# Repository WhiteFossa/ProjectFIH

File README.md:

# ProjectFIH
Digitally-controlled thermostat for heating outdoor hardware

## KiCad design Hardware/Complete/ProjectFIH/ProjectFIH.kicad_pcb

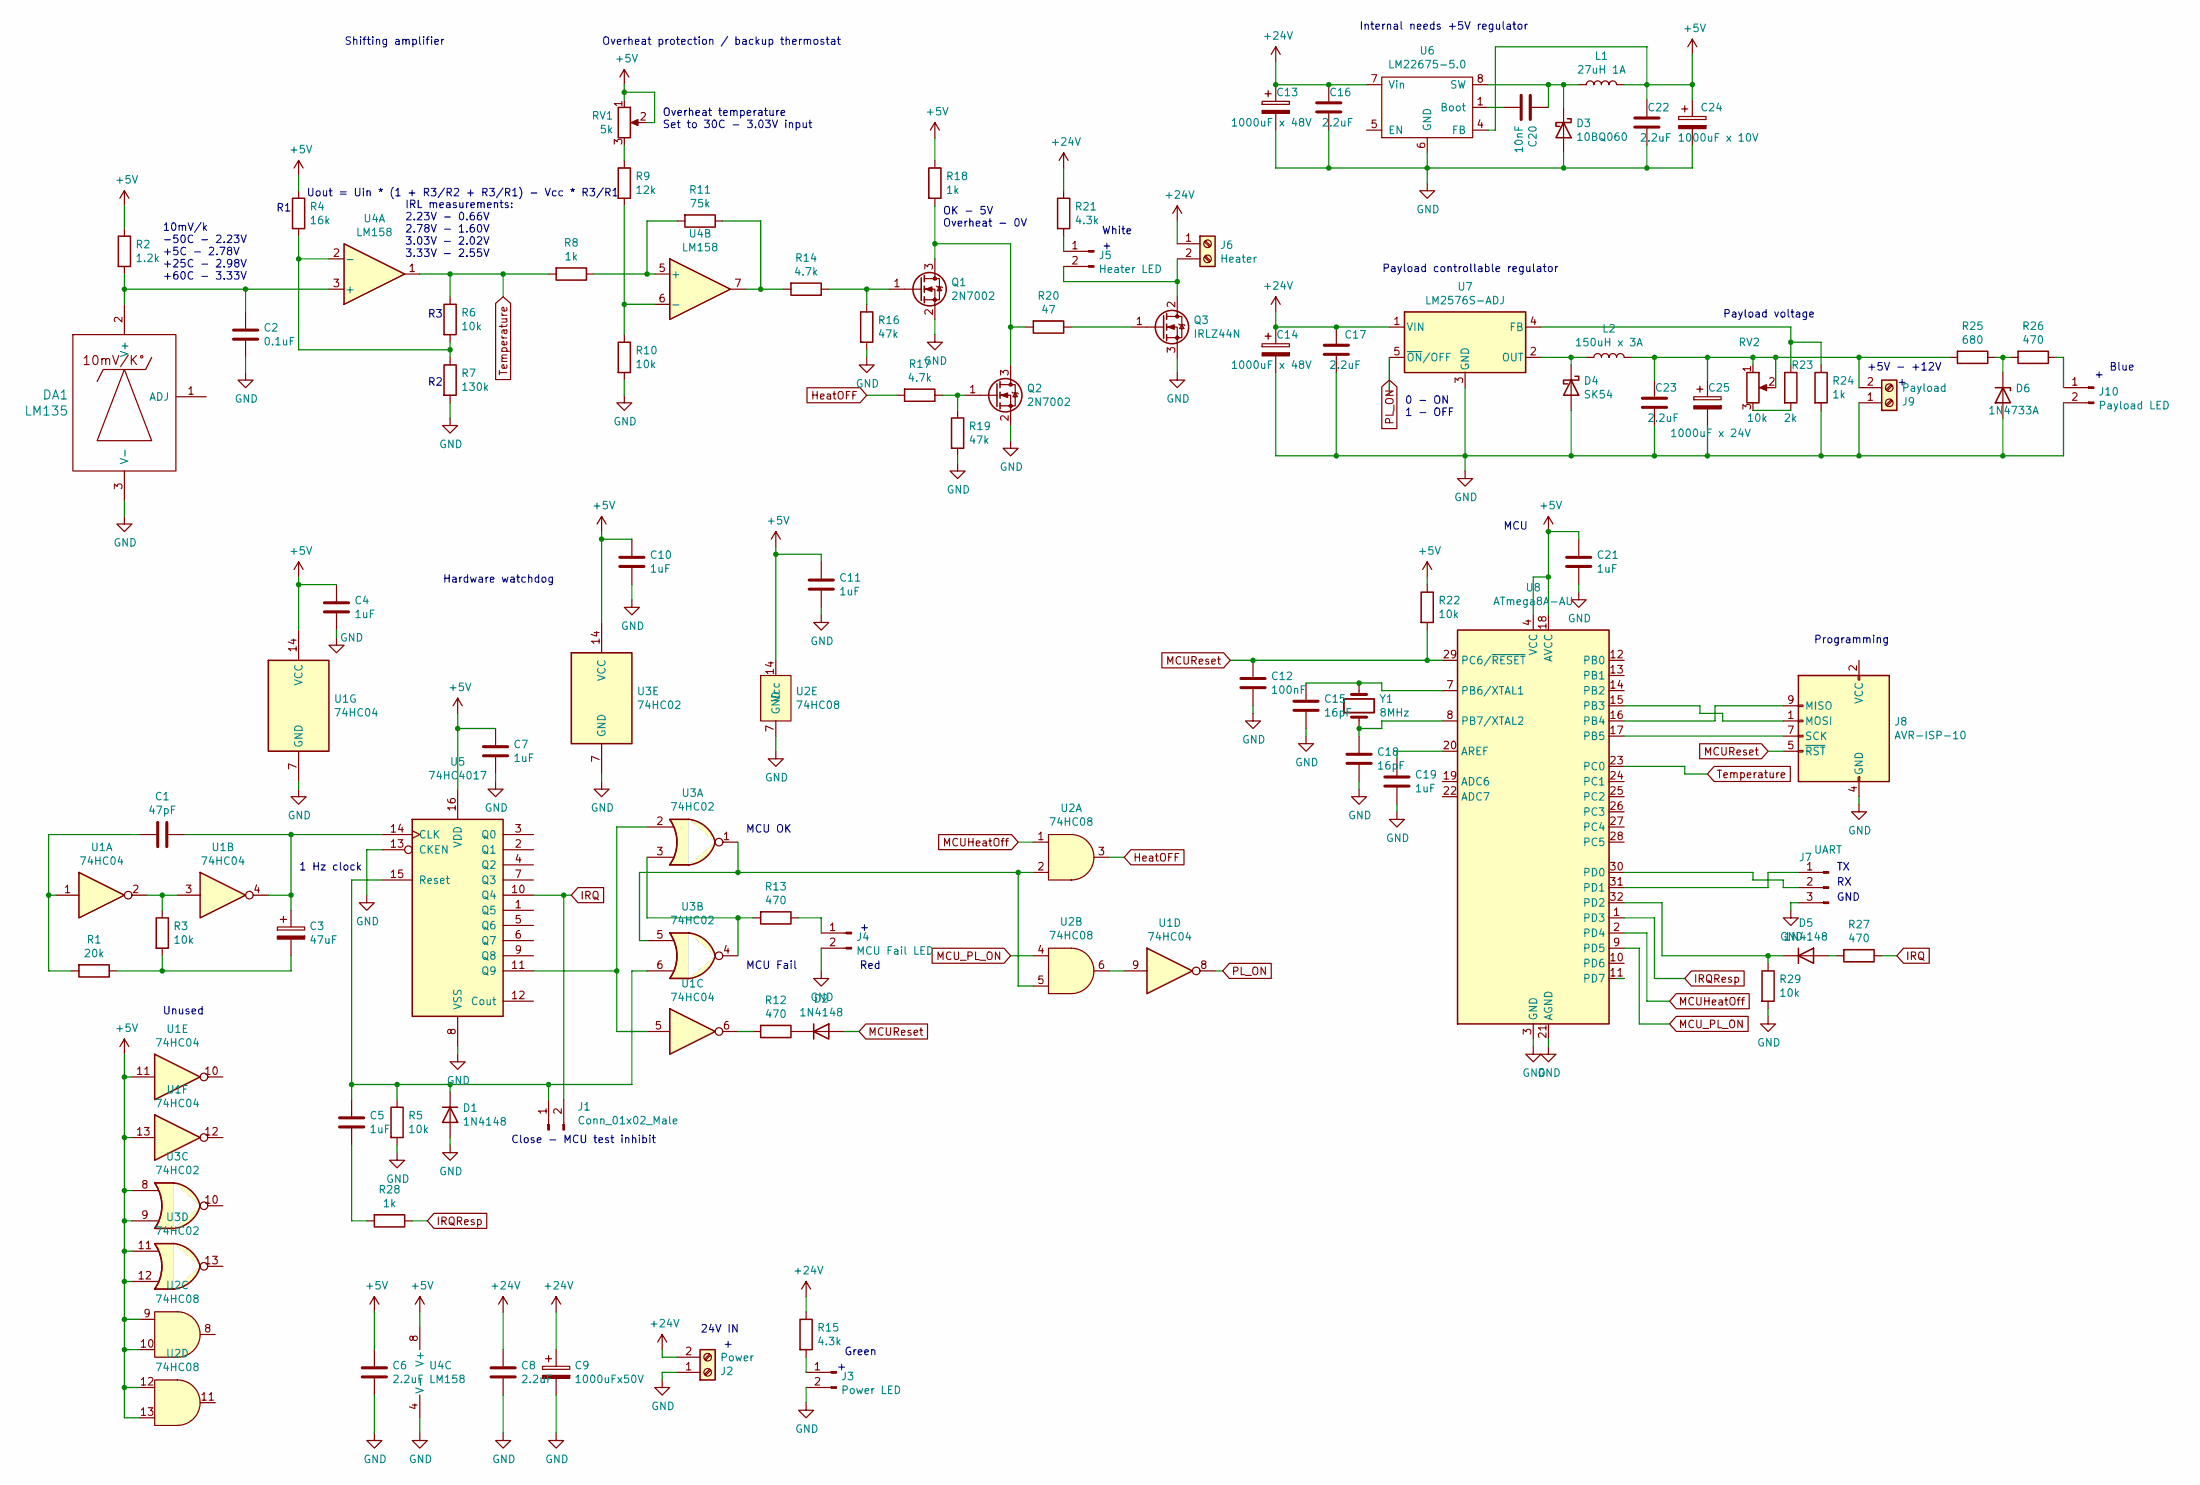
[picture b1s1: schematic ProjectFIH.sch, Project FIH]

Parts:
C1: 47pF; C_0805_2012Metric_Pad1.15x1.40mm_HandSolder
C2: 0.1uF; C_0805_2012Metric_Pad1.15x1.40mm_HandSolder
C3: 47uF; CP_Elec_4x5.7
C4, C5, C7, C10, C11, C19, C21: 1uF; C_0805_2012Metric_Pad1.15x1.40mm_HandSolder
C6, C8, C16, C17, C22, C23: 2.2uF; C_0805_2012Metric_Pad1.15x1.40mm_HandSolder
C9: 1000uFx50V; CP_Radial_D12.5mm_P5.00mm
C12: 100nF; C_0805_2012Metric_Pad1.15x1.40mm_HandSolder
C13, C14: 1000uF x 48V; CP_Radial_D12.5mm_P5.00mm
C15, C18: 16pF; C_0805_2012Metric_Pad1.15x1.40mm_HandSolder
C20: 10nF; C_0805_2012Metric_Pad1.15x1.40mm_HandSolder
C24: 1000uF x 10V; CP_Radial_D10.0mm_P5.00mm
C25: 1000uF x 24V; CP_Radial_D10.0mm_P5.00mm
D1, D2, D5: 1N4148; D_1210_3225Metric
D3: 10BQ060; D_SMB
D4: SK54; D_SMC
D6: 1N4733A; D_1210_3225Metric
DA1: LM135; TO-92
J1: Conn_01x02_Male; PinHeader_1x02_P2.54mm_Vertical
J2: Power; TerminalBlock_Altech_AK300-2_P5.00mm
J3: Power LED; PinHeader_1x02_P2.54mm_Vertical
J4: MCU Fail LED; PinHeader_1x02_P2.54mm_Vertical
J5: Heater LED; PinHeader_1x02_P2.54mm_Vertical
J6: Heater; TerminalBlock_Altech_AK300-2_P5.00mm
J7: UART; PinHeader_1x03_P2.54mm_Vertical
J8: AVR-ISP-10; IDC-Header_2x05_P2.54mm_Vertical
J9: Payload; TerminalBlock_Altech_AK300-2_P5.00mm
J10: Payload LED; PinHeader_1x02_P2.54mm_Vertical
L1: 27uH 1A; L_Radial_D10.0mm_P5.00mm_Fastron_07M
L2: 150uH x 3A; L_Radial_D16.8mm_P11.43mm_Vishay_IHB-1
Q1, Q2: 2N7002; SOT-23
Q3: IRLZ44N; TO-220-3_Horizontal_TabDown
R1: 20k; R_0805_2012Metric_Pad1.15x1.40mm_HandSolder
R2: 1.2k; R_0805_2012Metric_Pad1.15x1.40mm_HandSolder
R3, R5, R6, R10, R22, R29: 10k; R_0805_2012Metric_Pad1.15x1.40mm_HandSolder
R4: 16k; R_0805_2012Metric_Pad1.15x1.40mm_HandSolder
R7: 130k; R_0805_2012Metric_Pad1.15x1.40mm_HandSolder
R8, R18, R24, R28: 1k; R_0805_2012Metric_Pad1.15x1.40mm_HandSolder
R9: 12k; R_0805_2012Metric_Pad1.15x1.40mm_HandSolder
R11: 75k; R_0805_2012Metric_Pad1.15x1.40mm_HandSolder
R12, R13, R26, R27: 470; R_0805_2012Metric_Pad1.15x1.40mm_HandSolder
R14, R17: 4.7k; R_0805_2012Metric_Pad1.15x1.40mm_HandSolder
R15, R21: 4.3k; R_0805_2012Metric_Pad1.15x1.40mm_HandSolder
R16, R19: 47k; R_0805_2012Metric_Pad1.15x1.40mm_HandSolder
R20: 47; R_0805_2012Metric_Pad1.15x1.40mm_HandSolder
R23: 2k; R_0805_2012Metric_Pad1.15x1.40mm_HandSolder
R25: 680; R_0805_2012Metric_Pad1.15x1.40mm_HandSolder
RV1: 5k; Potentiometer_Bourns_3296W_Vertical
RV2: 10k; Potentiometer_Bourns_3296W_Vertical
U1: 74HC04; SOIC-14_3.9x8.7mm_P1.27mm
U2: 74HC08; SOIC-14_3.9x8.7mm_P1.27mm
U3: 74HC02; SOIC-14_3.9x8.7mm_P1.27mm
U4: LM158; SOIJ-8_5.3x5.3mm_P1.27mm
U5: 74HC4017; SOIC-16_4.55x10.3mm_P1.27mm
U6: LM22675-5.0; SOIC-8_3.9x4.9mm_P1.27mm
U7: LM2576S-ADJ; TO-263-5_TabPin3
U8: ATmega8A-AU; TQFP-32_7x7mm_P0.8mm
Y1: 8MHz; Crystal_HC49-4H_Vertical

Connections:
+5V: C4.1, C6.1, C7.1, C10.1, C11.1, C21.1, C22.1, C24.1, L1.2, R2.1, R4.1, R18.1, R22.1, RV1.1, RV1.2, U1.11, U1.13, U1.14 (VCC), U2.9, U2.10, U2.12, U2.13, U2.14 (Vcc), U3.8, U3.9, U3.11, U3.12, U3.14 (VCC), U4.8 (V+), U5.16 (VDD), U6.4 (FB), U8.4 (VCC), U8.6 (VCC), U8.18 (AVCC)
+24V: C8.1, C9.1, C13.1, C14.1, C16.1, C17.1, J2.2, J6.1, R15.1, R21.1, U6.7 (Vin), U7.1 (VIN)
GND: C2.2, C4.2, C6.2, C7.2, C8.2, C9.2, C10.2, C11.2, C12.2, C13.2, C14.2, C15.2, C16.2, C17.2, C18.2, C19.2, C21.2, C22.2, C23.2, C24.2, C25.2, D1.2 (A), D3.2 (A), D4.2 (A), D6.2 (A), DA1.3 (V-), J2.1, J3.2, J4.2, J7.3, J8.4 (GND), J8.6 (GND), J8.8 (GND), J8.10 (GND), J9.1, J10.2, Q1.2 (S), Q2.2 (S), Q3.3 (S), R5.2, R7.2, R10.2, R16.2, R19.2, R24.2, R29.2, U1.7 (GND), U2.7 (GND), U3.7 (GND), U4.4 (V-), U5.8 (VSS), U5.13 (CKEN), U6.6 (GND), U7.3 (GND), U8.3 (GND), U8.5 (GND), U8.21 (AGND)
HeatOFF: R17.2, U2.3
IRQ: J1.2, R27.1, U5.10 (Q4)
IRQResp: R28.1, U8.1 (PD3)
MCUHeatOff: U2.1, U8.2 (PD4)
MCUReset: C12.1, D2.2 (A), J8.5 (~RST), R22.2, U8.29 (PC6/~RESET)
MCU_PL_ON: U2.4, U8.9 (PD5)
unnamed: C1.1, C3.1, U1.4, U5.14 (CLK)
unnamed: C1.2, R1.2, U1.1
unnamed: C2.1, DA1.2 (V+), R2.2, U4.3 (+)
unnamed: C3.2, R1.1, R3.2
unnamed: C5.1, D1.1 (K), J1.1, R5.1, U3.6, U5.15 (Reset)
unnamed: C5.2, R28.2
unnamed: C15.1, U8.7 (PB6/XTAL1), Y1.2
unnamed: C18.1, U8.8 (PB7/XTAL2), Y1.1
unnamed: C19.1, U8.20 (AREF)
unnamed: C20.1, D3.1 (K), L1.1, U6.8 (SW)
unnamed: C20.2, U6.1 (Boot)
unnamed: C23.1, C25.1, J9.2, L2.2, R25.2, RV2.1, RV2.2
unnamed: D2.1 (K), R12.1
unnamed: D4.1 (K), L2.1, U7.2 (OUT)
unnamed: D5.1 (K), R29.1, U8.32 (PD2)
unnamed: D5.2 (A), R27.2
unnamed: D6.1 (K), R25.1, R26.2
unnamed: J3.1, R15.2
unnamed: J4.1, R13.1
unnamed: J5.1, R21.2
unnamed: J5.2, J6.2, Q3.2 (D)
unnamed: J7.1, U8.31 (PD1)
unnamed: J7.2, U8.30 (PD0)
unnamed: J8.1 (MOSI), U8.15 (PB3)
unnamed: J8.7 (SCK), U8.17 (PB5)
unnamed: J8.9 (MISO), U8.16 (PB4)
unnamed: J10.1, R26.1
unnamed: Q1.1 (G), R14.1, R16.1
unnamed: Q1.3 (D), Q2.3 (D), R18.2, R20.2
unnamed: Q2.1 (G), R17.1, R19.1
unnamed: Q3.1 (G), R20.1
unnamed: R3.1, U1.2, U1.3
unnamed: R4.2, R6.2, R7.1, U4.2 (-)
unnamed: R9.1, RV1.3
unnamed: R9.2, R10.1, U4.6 (-)
unnamed: R11.1, R14.2, U4.7
unnamed: R8.1, R11.2, U4.5 (+)
unnamed: R12.2, U1.6
unnamed: R13.2, U3.3, U3.4
unnamed: R23.1, R24.1, U7.4 (FB)
unnamed: R23.2, RV2.3
unnamed: U1.5, U3.2, U5.11 (Q9)
unnamed: U1.9, U2.6
unnamed: U2.2, U2.5, U3.1, U3.5
PL_ON: U1.8, U7.5 (~ON~/OFF)
Temperature: R6.1, R8.2, U4.1, U8.23 (PC0)

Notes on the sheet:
Uout = Uin * (1 + R3/R2 + R3/R1) - Vcc * R3/R1
10mV/k -50C - 2.23V +5C - 2.78V +25C - 2.98V +60C - 3.33V
IRL measurements: 2.23V - 0.66V 2.78V - 1.60V 3.03V - 2.02V 3.33V - 2.55V
OK - 5V Overheat - 0V
Internal needs +5V regulator
0 - ON 1 - OFF
Payload controllable regulator
+5V - +12V
1 Hz clock
MCU Fail
MCU OK
Close - MCU test inhibit
Overheat protection / backup thermostat
Shifting amplifier
Hardware watchdog
Unused
GND
Programming
MCU
24V IN
Red
Green
White
Blue
Payload voltage
Overheat temperature Set to 30C - 3.03V input

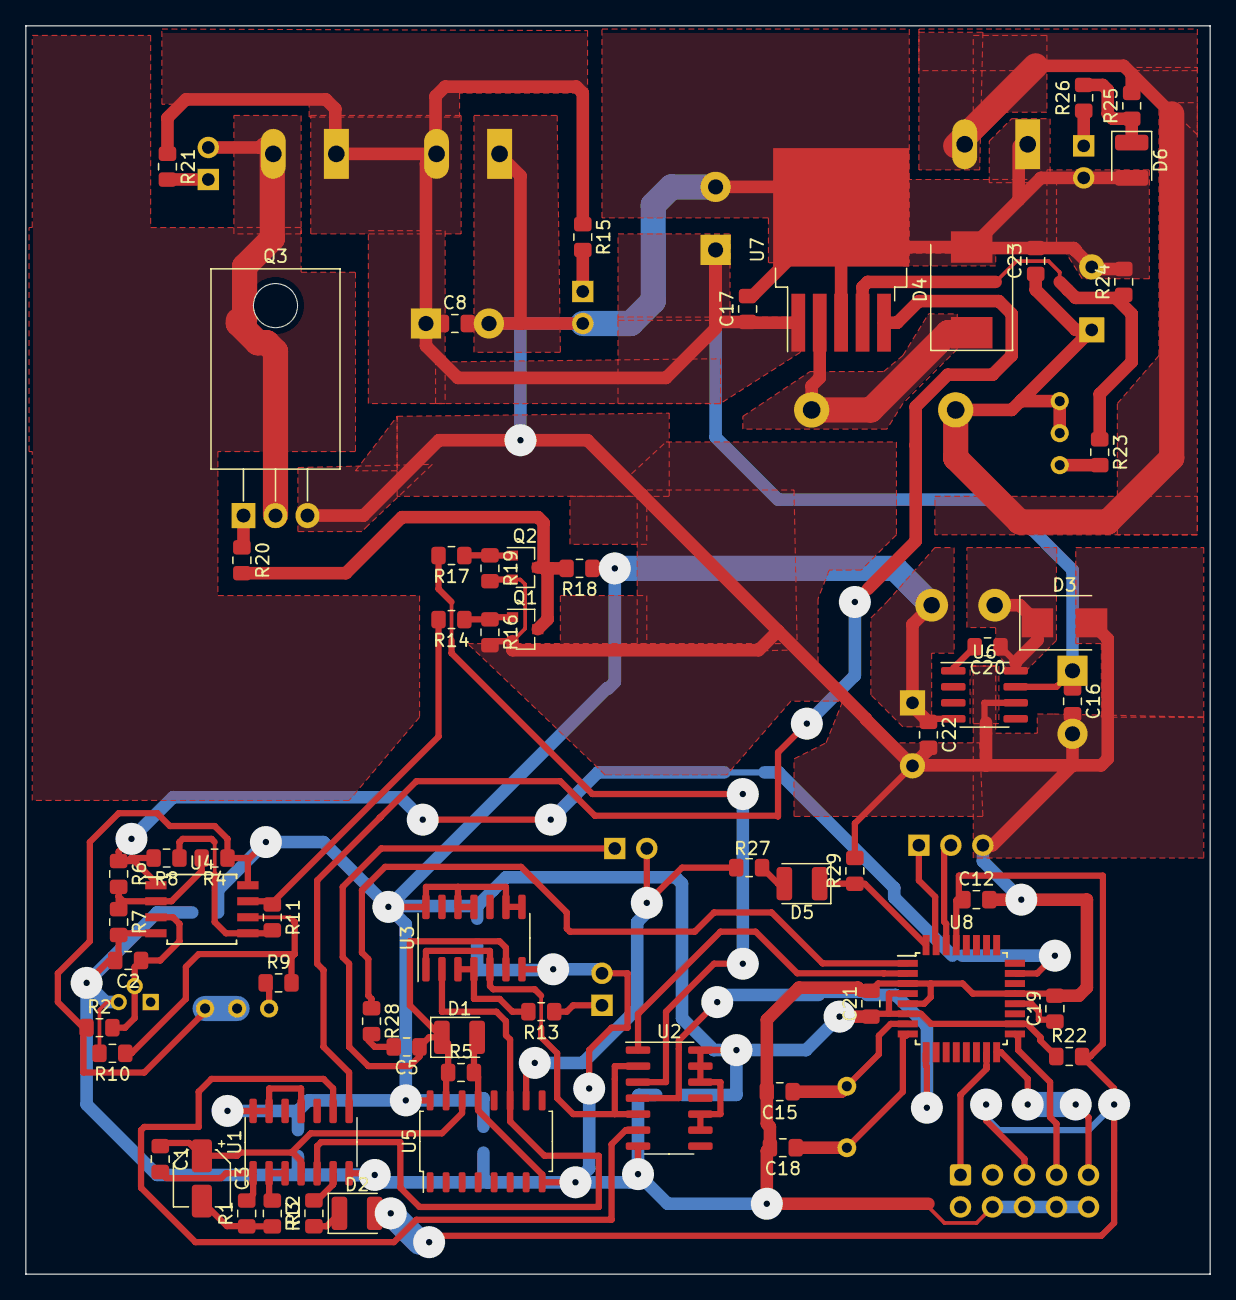
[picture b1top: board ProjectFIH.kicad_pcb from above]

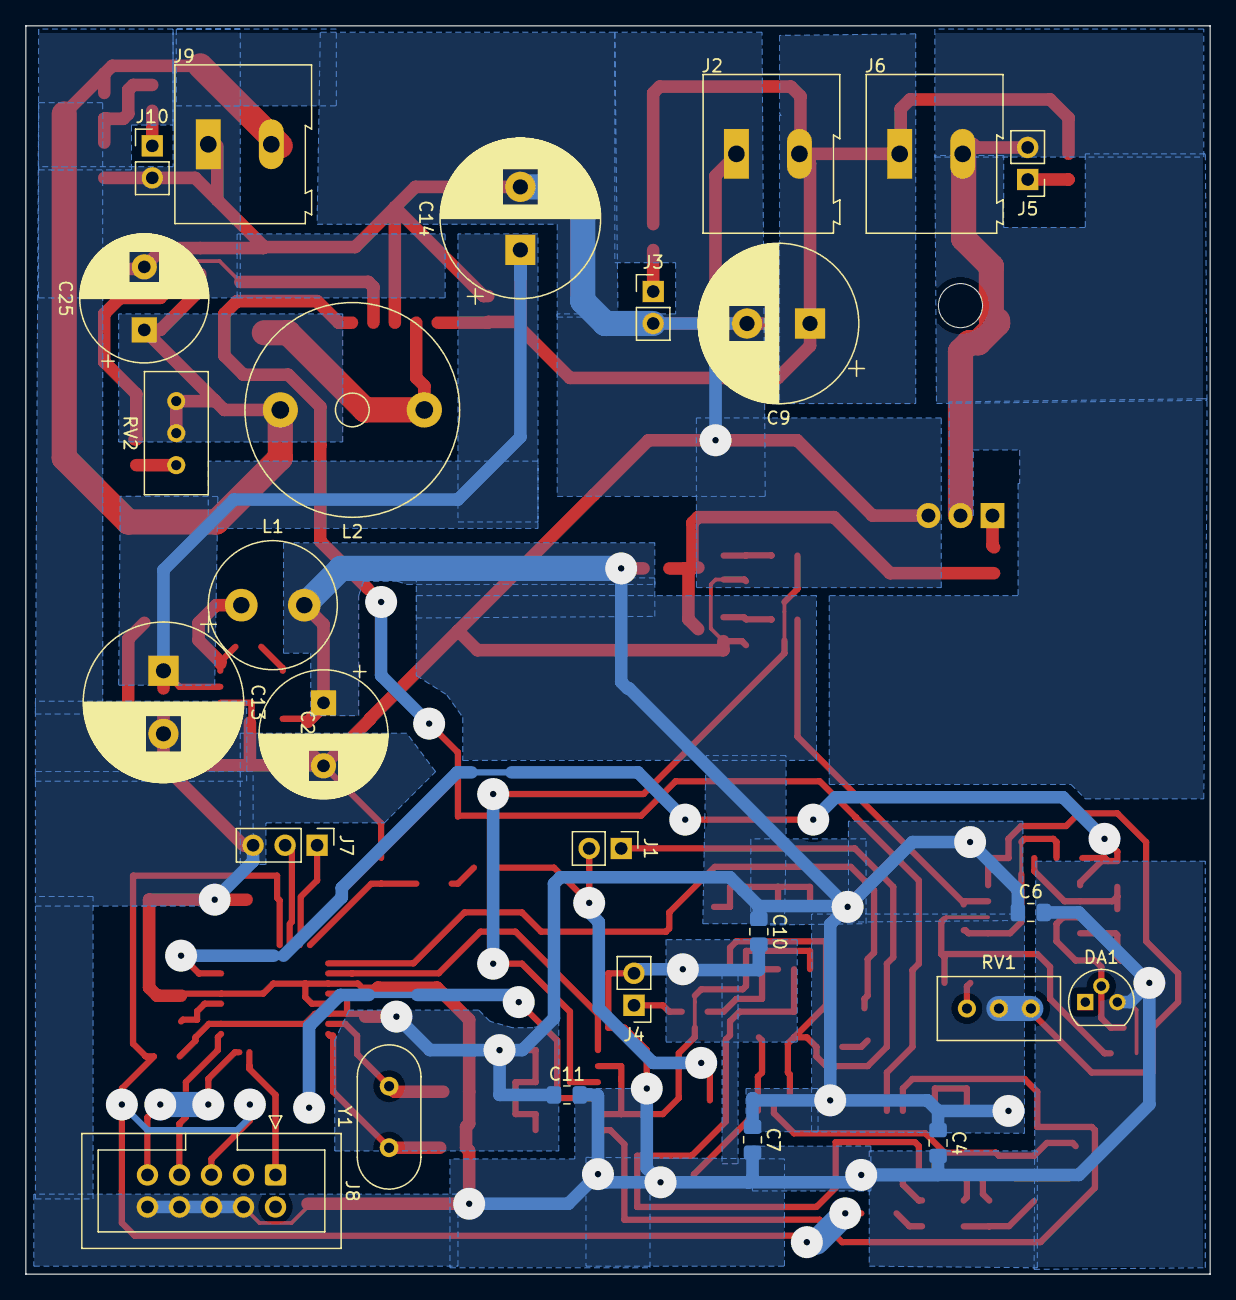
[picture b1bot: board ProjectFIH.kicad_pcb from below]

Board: 2 copper layers, 94.0 x 99.1 mm, 87 parts (26 on the bottom side), 55 nets.

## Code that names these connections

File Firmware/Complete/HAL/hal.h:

/*
 * hal.h
 *
 * Hardware Abstraction Layer
 *
 *  Created on: Sep 6, 2020
 *      Author: fossa
 */

#ifndef HAL_HAL_H_
#define HAL_HAL_H_

/**
 * Includes
 */

#include <avr/io.h> /* Common */
#include <avr/interrupt.h> /* Interrupts support */
#include <stdio.h> /* I/O over UART */

/**
 * End of includes
 */

/**
 *  MCU Frequency
 */
#define F_CPU 8000000UL

/**
 * UART baudrate
 */
#define BAUD 9600

#include <util/setbaud.h> /* Baudrate macroses */

/**
 * Ports:
 * PC0 - Temperature input (ADC)
 *
 * PD0 - UART RX (input)
 * PD1 - UART TX (output)
 * PD2 - HWDT (Hardware WatchDog Timer) IRQ Request (input, INT0)
 * PD3 - HWDT IRQ Response (output)
 * PD4 - Heater off (output)
 * PD5 - Payload on (output)
 */

/**
 * ADC-related data:
 * Vref = 2.56V
 *
 *	Temp	LM135	ADCin	Code
 *	-50		2.23	0.66	264
 *	+5		2.78	1.60	640
 *	+25		2.98	2.02	808
 *	+60		3.33	2.55	1020
 *
 * ADC = 6.873 * Tcelsius + 607.64
 *
 * Delta(ADC-per-Celsius) = 6.873
 *
 */

/* Boolean */
#define bool uint8_t
#define true 0xFFU
#define false 0x00U

/** !!!!!!!!!!!!!!!!!!!!!!!!!!!!!!!!!!!!!!!!!!!!!!!!!!!!!!!!!!
 *  !!PORTS DIRECTIONS - WRONG SETTINGS WILL DAMAGE HARDWARE!!
 *  !!!!!!!!!!!!!!!!!!!!!!!!!!!!!!!!!!!!!!!!!!!!!!!!!!!!!!!!!!
 */
#define HAL_PORTB_DIR 0b00000000
#define HAL_PORTC_DIR 0b00000000
#define HAL_PORTD_DIR 0b00111010

/**
 * Ports and pins for various signals
 */

/* HWDT IRQ Response signal is on this port */
#define HAL_HWDT_IRQ_RESP_PORT PORTD

/* Heater off signal is on this port */
#define HAL_HEATER_OFF_PORT PORTD

/* Payload on signal is on this port */
#define HAL_PAYLOAD_ON_PORT PORTD

/* HWDT IRQ Response signal pin */
#define HAL_HWDT_IRQ_RESP_PIN 3

/* Heater off signal pin */
#define HAL_HEATER_OFF_PIN 4

/* Payload on signal pin */
#define HAL_PAYLOAD_ON_PIN 5


/* States for HWDT IRQ Resp state machine */
#define HAL_HWDT_IRQRESP_SM_STANDBY 0U /* Standby for IRQ, IRQRESP low */
#define HAL_HWDT_IRQRESP_SM_PRE_PULSE 1U /* After IRQ, pre pulse, IRQRESP low */
#define HAL_HWDT_IRQRESP_SM_PULSE 2U /* Pulse, IRQRESP high */
#define HAL_HWDT_IRQRESP_SM_POST_PULSE 3U /* Post pulse, IRQRESP low */

/* Temperature conversion related constants */
#define HAL_ADC_AVERAGING_WINDOW_LENGTH 16U /* Averaging window length*/

/**
 * Variables
 */

/* HWDT IRQ Resp state machine state */
volatile uint8_t hal_hwdt_irqresp_state_machine_state;

/* ADC averaging window */
volatile uint16_t hal_adc_averaging_window[HAL_ADC_AVERAGING_WINDOW_LENGTH];

/* ADC average value, multiplied by window length. */
volatile int32_t hal_adc_average_value_multiplied;

/* Averaged ADC value, use it to temperature measurements */
volatile uint16_t hal_adc_average;


/**
 * Functions (public)
 */

/**
 * Initialized hardware (port directions and so on).
 */
void hal_init();

/**
 * Heater control.
 */
void hal_heater_on();
void hal_heater_off();
bool hal_is_heater_on();


/**
 * Payload control.
 */
void hal_payload_on();
void hal_payload_off();
bool hal_is_payload_on();

/**
 * HWDT IRQ Resp low-level control
 */
void hal_pull_hwdt_irqresp_up();
void hal_pull_hwdt_irqresp_down();

/* Returns current temperature (as ADC readings) */
uint16_t hal_get_temperature();

/**
 * Functions (private)
 */

/* Put character into stream */
static int hal_uart_putchar(char c, FILE *stream);

/* Streams */
static FILE hal_uart_stdout = FDEV_SETUP_STREAM(hal_uart_putchar, NULL, _FDEV_SETUP_WRITE);

#endif /* HAL_HAL_H_ */

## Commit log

2020-06-27 Added first (obsolete) idea.
2020-06-27 Added second idea (actual)
2020-07-01 Scaling amplifier simulation
2020-07-01 Started to draw device circuit diagram
2020-07-01 Found that real LM358 saturates at 0.6V output (low). So, recalculated and retested.
2020-07-01 Comparer for overheat protection (simulation).
2020-07-03 Overheat protection comparator
2020-07-04 Corrected hysterezis loop resistor.
2020-07-04 Output stage, heat control.
2020-07-11 Added 24 -> 5 regulator
2020-07-11 Added payload regulator
2020-07-14 Added hardware watchdog
2020-07-17 Fixed incorrect counter reset.
    Ready to add MCU and start PCB tracing
2020-07-19 Schematic seems to be completed
2020-07-21 Added LEDs
2020-07-23 Assigned some cases
2020-07-24 Cases assigned
2020-07-24 Fixed label and generated netlist
2020-07-24 Started to trace PCB
2020-07-25 Partially routed PCB
2020-07-27 More tracing
2020-08-01 Before coupling MCU with hardware watchdog
2020-08-01 MCU coupled with hardware watchdog
2020-08-02 Need to connect units
2020-08-02 Tracing done except widening and filling
2020-08-03 Small corrections after laying IRL parts out
2020-08-04 Started tracks widening and filling
2020-08-05 Flipped some (but not all needed) parts to other side
2020-08-05 Everything is on correct sides
2020-08-05 Partially metallized empty spaces.
2020-08-05 Most of metallization
2020-08-06 Filled. Imperfect, but don't want to re-do.
2020-08-06 Prepared phototemplates
2020-08-07 Gerber files
2020-08-15 Generated a BOM
2020-08-15 LM335 -> LM135
2020-08-16 Small PCB optimization
2020-08-25 Small comments on schematic
2020-08-29 Small corrections
2020-08-29 Updated BOM
2020-08-30 Swapped outputs of U3
2020-09-08 Early firmware development.
2020-09-09 Important schematics and PCB fixes + some firmware development.
2020-09-10 MCU is able to keep HWDT under control.
2020-09-13 Correct ADC averaging.
2020-09-13 Payload and heater temperature control

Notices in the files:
Hardware/Complete/ProjectFIH/ProjectFIH.sch:
AGPL
